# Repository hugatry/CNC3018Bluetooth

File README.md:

# CNC3018Bluetooth
 HM-10 based bluetooth module for CNC 3018 (Pro). Works with Woodpecker 3.4 and other compatible CNC controller boards.
 
 [Video introducing/testing this project](https://youtu.be/gbWO2Mq1XHM)

## HM-10 configuration
 This add-on module is ment to be used with HM-10 based USB dongle.
 Starting from HM-10 default configuration, CNC add-on module works as is, but USB-dongle needs to be set as Central/Master with "AT+ROLE1".
 
 It's recommended to use firmware version V700 or newer, which has correct baud rate and possibly other configurations as default. Hm-10 modules with older firmware may or may not work.
 
 ## Changes after the video, before the initial commit:
 * Ground pour removed behind the antenna
 * HM-10 ground pads are actually connected to the circuit :)

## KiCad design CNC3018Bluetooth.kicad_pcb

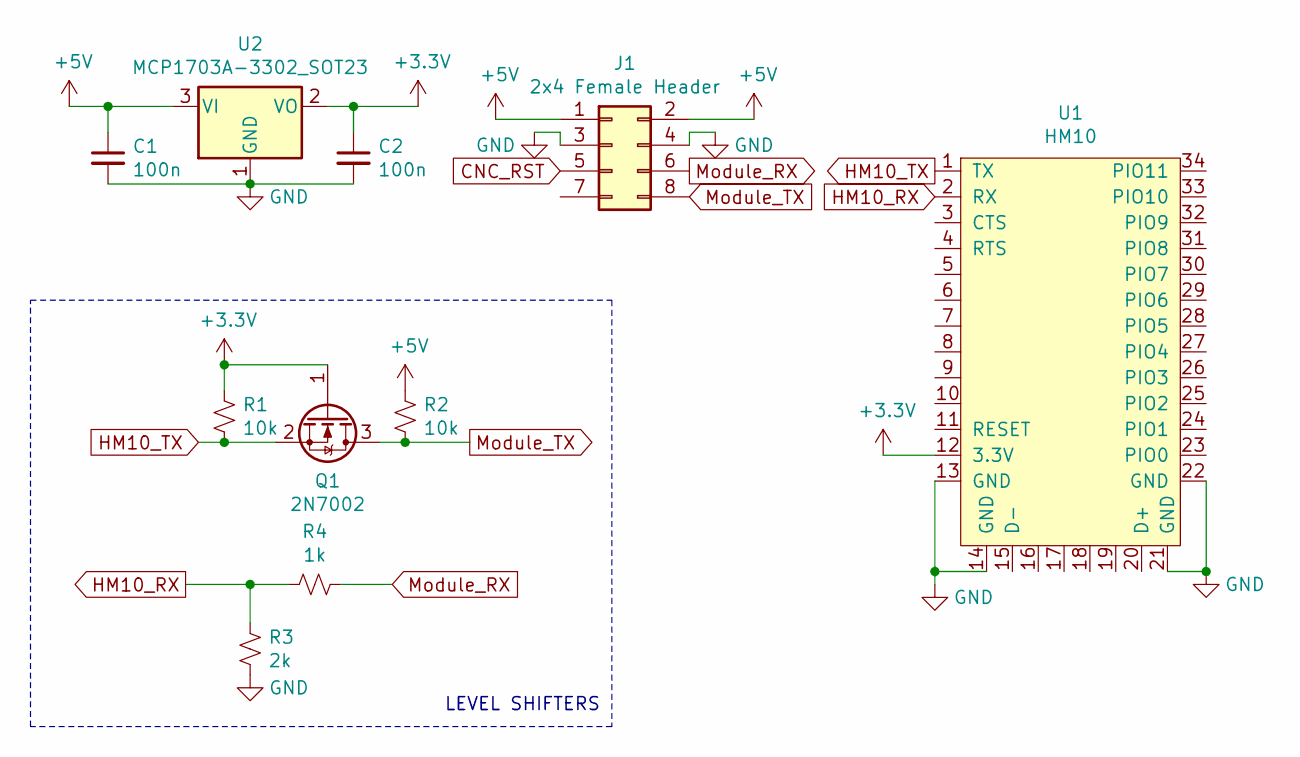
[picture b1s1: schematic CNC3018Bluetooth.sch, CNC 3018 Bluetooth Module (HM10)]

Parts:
C1, C2: 100n; C_0603_1608Metric
J1: 2x4 Female Header; PinSocket_2x04_P2.54mm_Vertical
Q1: 2N7002; SOT-23
R1, R2: 10k; R_0603_1608Metric
R3: 2k; R_0603_1608Metric
R4: 1k; R_0603_1608Metric
U1: HM10
U2: MCP1703A-3302_SOT23; SOT-23

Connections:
+3V3: C2.1, Q1.1 (G), R1.1, U1.12 (3.3V), U2.2 (VO)
+5V: C1.1, J1.1, J1.2, R2.1, U2.3 (VI)
CNC_RST: J1.5
GND: C1.2, C2.2, J1.3, J1.4, R3.1, U1.13 (GND), U1.14 (GND), U1.21 (GND), U1.22 (GND), U2.1 (GND)
HM10_RX: R3.2, R4.2, U1.2 (RX)
HM10_TX: Q1.2 (S), R1.2, U1.1 (TX)
Module_RX: J1.6, R4.1
Module_TX: J1.8, Q1.3 (D), R2.2

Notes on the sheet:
LEVEL SHIFTERS

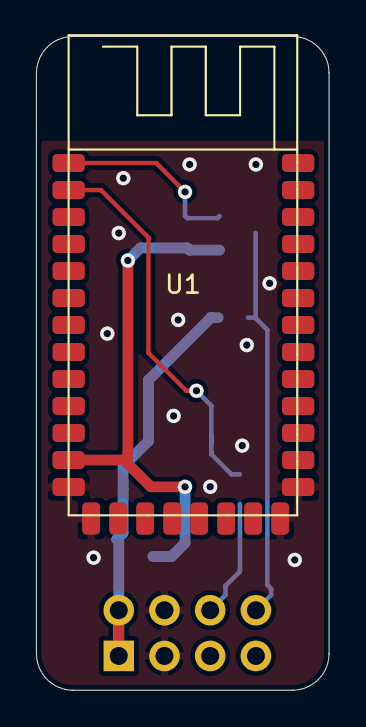
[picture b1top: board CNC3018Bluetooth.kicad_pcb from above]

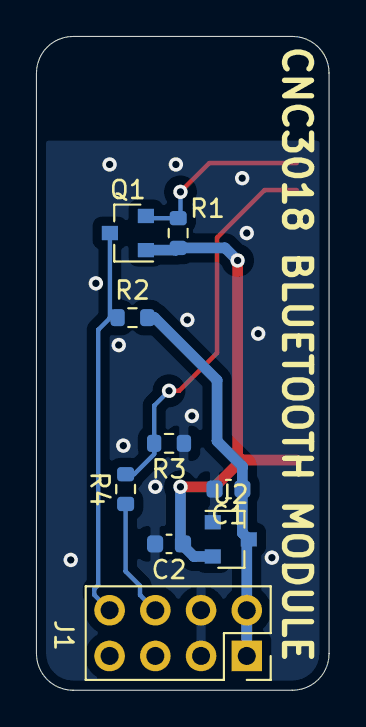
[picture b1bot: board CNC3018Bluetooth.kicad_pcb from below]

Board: 2 copper layers, 16.3 x 36.3 mm, 10 parts (9 on the bottom side), 7 nets.

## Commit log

2021-06-10 Update README.md
    README, initial details
2021-06-10 README updated: Changse after video
